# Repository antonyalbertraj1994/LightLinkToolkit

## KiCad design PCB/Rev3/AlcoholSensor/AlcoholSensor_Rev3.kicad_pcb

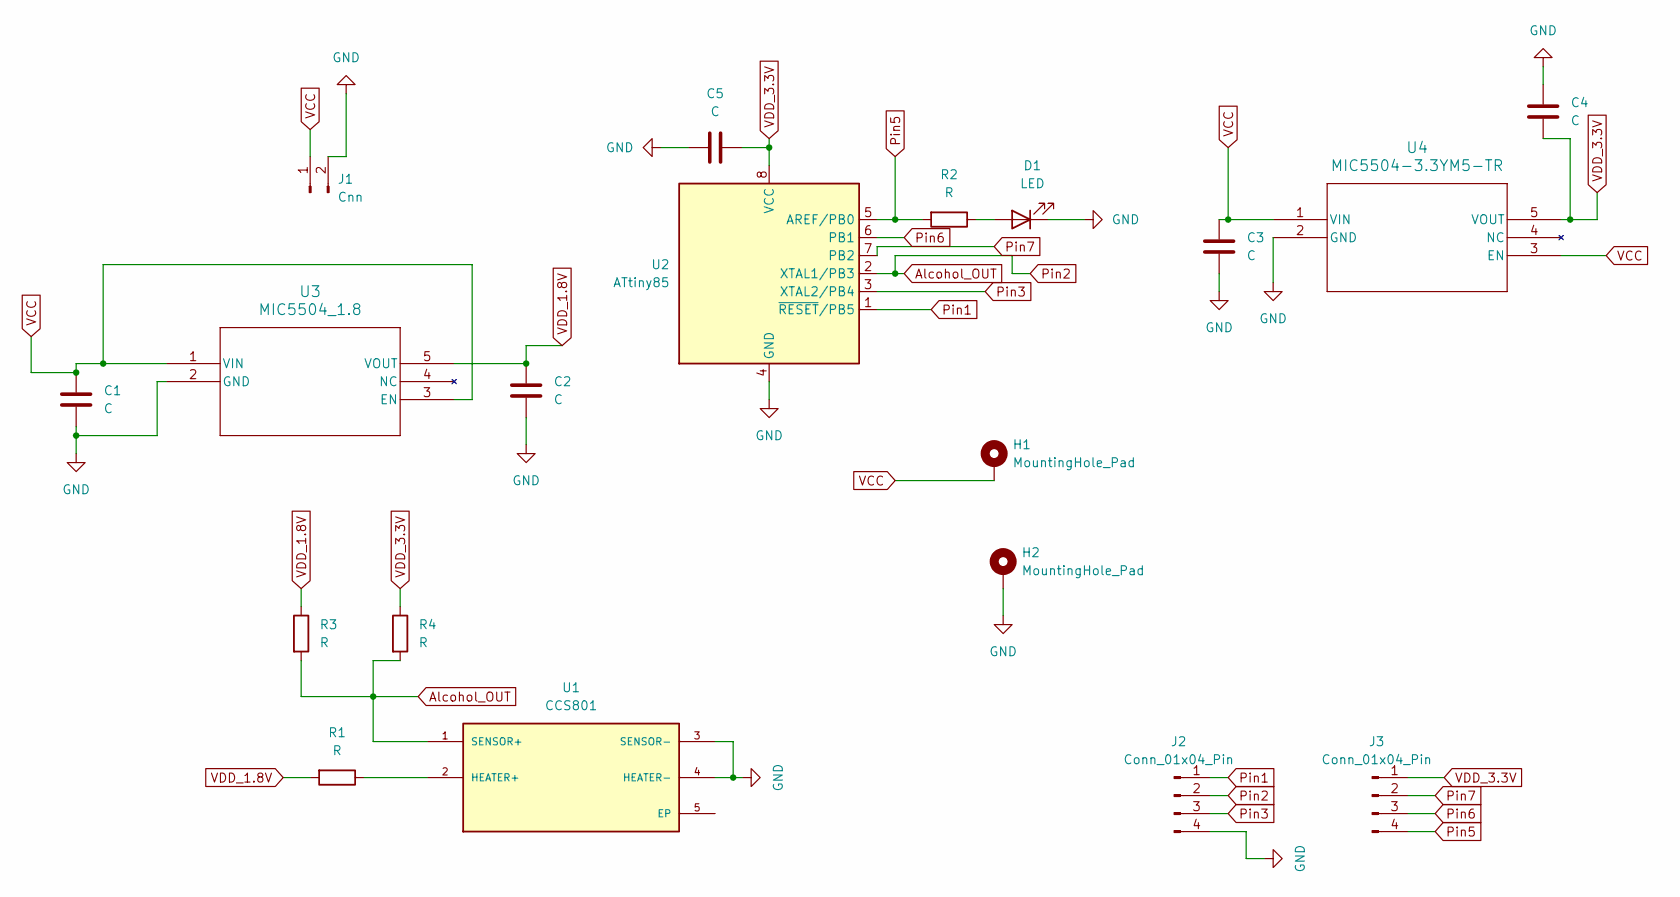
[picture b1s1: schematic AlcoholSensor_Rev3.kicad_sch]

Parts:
C1, C2, C3, C4, C5: C; C_0603_1608Metric_Pad1.08x0.95mm_HandSolder
D1: LED; LED_0805_2012Metric_Pad1.15x1.40mm_HandSolder
H1, H2: MountingHole_Pad; MT_Hole
J1: Cnn; PinHeader_1x02_P2.54mm_Vertical
J2, J3: Conn_01x04_Pin; PinHeader_1x04_P1.27mm_Vertical
R1, R2, R3, R4: R; R_0603_1608Metric_Pad0.98x0.95mm_HandSolder
U1: CCS801; XDCR_CCS801; PARTREV v1-04
U2: ATtiny85; SOIC-8W_5.3x5.3mm_P1.27mm
U3: MIC5504_1.8; SOT23-5LD-PL-1_MCH
U4: MIC5504-3.3YM5-TR; SOT-23-5_MC_MCH

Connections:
Alcohol_OUT: J2.2, R3.2, R4.2, U1.1 (SENSOR+), U2.2 (XTAL1/PB3)
GND: C1.2, C2.2, C3.2, C4.2, C5.1, D1.1 (K), H2.1, J1.2, J2.4, U1.3 (SENSOR-), U1.4 (HEATER-), U2.4 (GND), U3.2 (GND), U4.2 (GND)
unnamed: D1.2 (A), R2.1
unnamed: R1.1, U1.2 (HEATER+)
Pin1: J2.1, U2.1 (~RESET/PB5)
Pin3: J2.3, U2.3 (XTAL2/PB4)
Pin5: J3.4, R2.2, U2.5 (AREF/PB0)
Pin6: J3.3, U2.6 (PB1)
Pin7: J3.2, U2.7 (PB2)
VCC: C1.1, C3.1, H1.1, J1.1, U3.1 (VIN), U3.3 (EN), U4.1 (VIN), U4.3 (EN)
VDD_1.8V: C2.1, R1.2, R3.1, U3.5 (VOUT)
VDD_3.3V: C4.1, C5.2, J3.1, R4.1, U2.8 (VCC), U4.5 (VOUT)

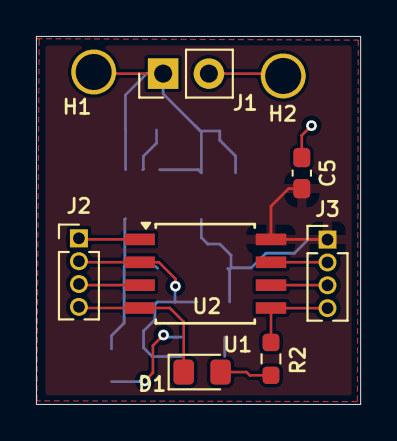
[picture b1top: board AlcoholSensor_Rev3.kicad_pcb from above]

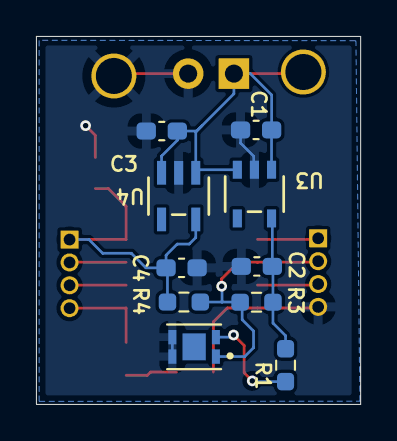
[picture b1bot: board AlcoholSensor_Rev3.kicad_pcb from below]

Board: 2 copper layers, 18.0 x 20.4 mm, 19 parts (10 on the bottom side), 12 nets.

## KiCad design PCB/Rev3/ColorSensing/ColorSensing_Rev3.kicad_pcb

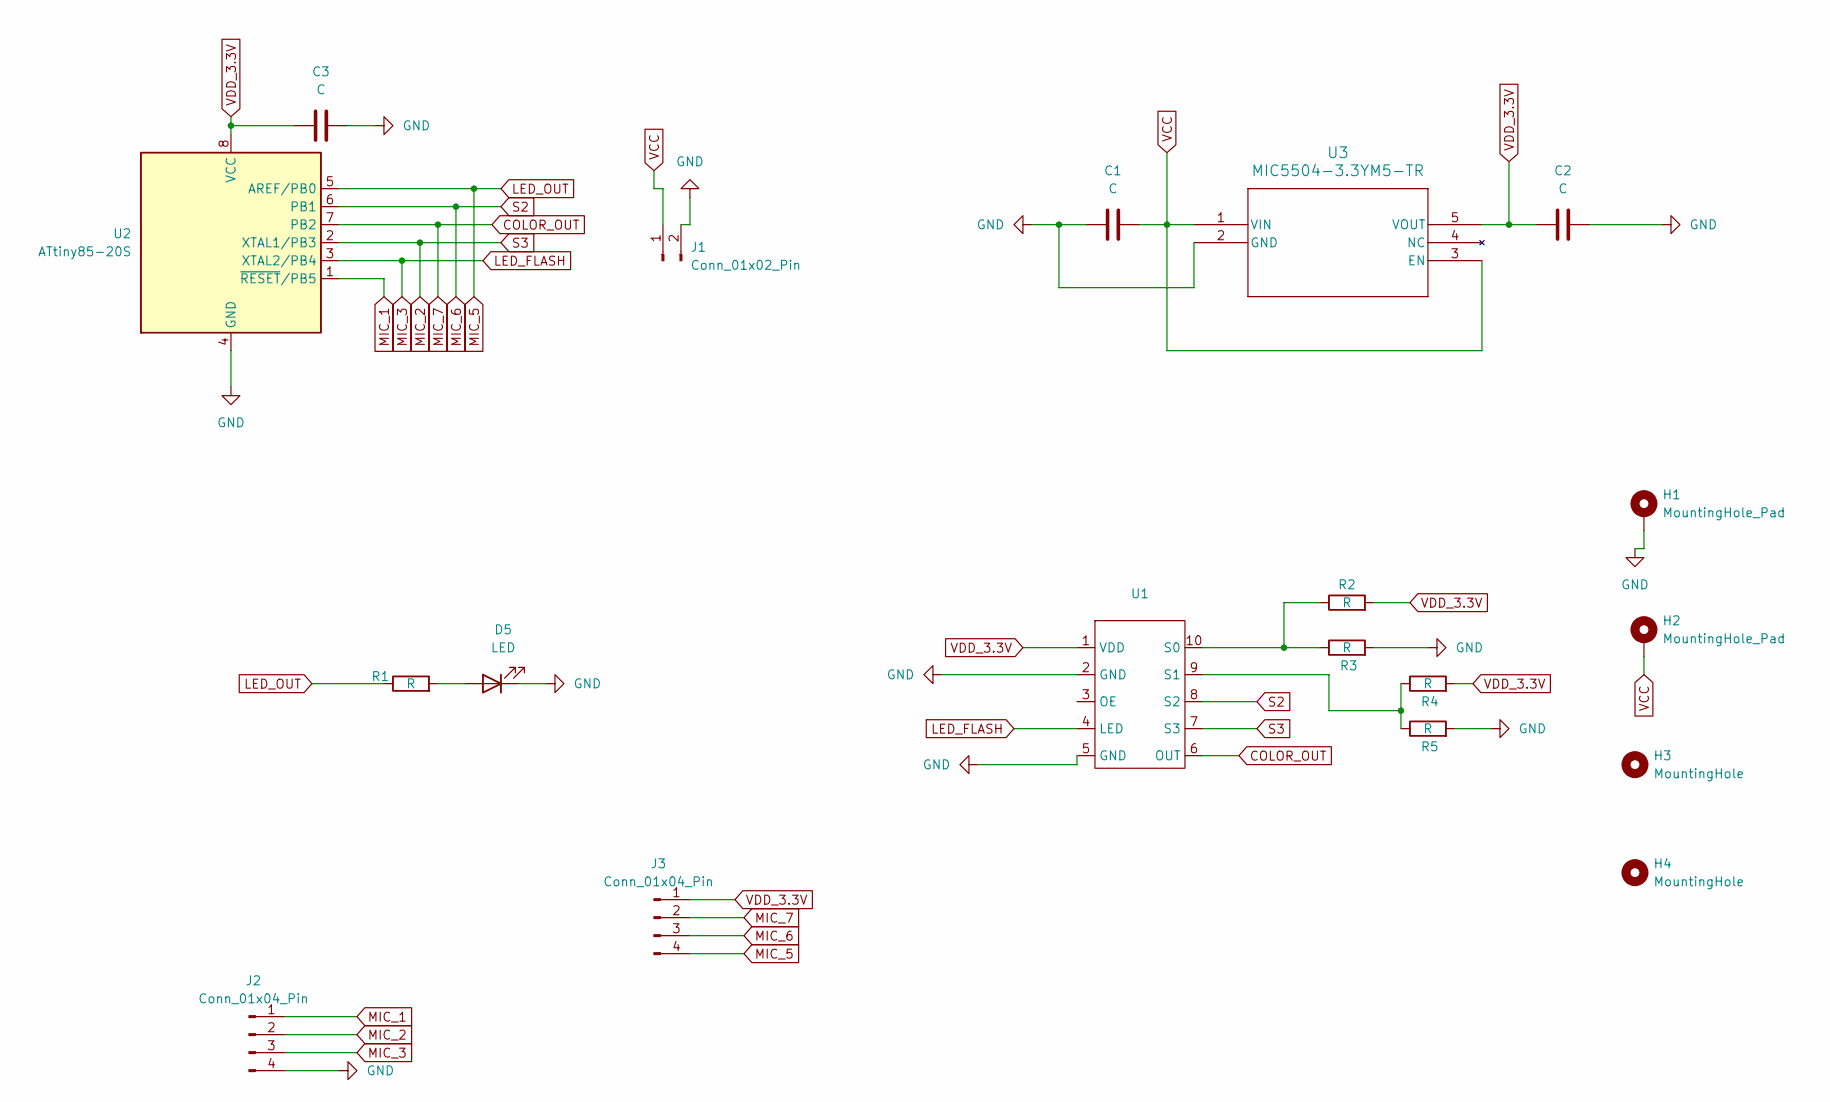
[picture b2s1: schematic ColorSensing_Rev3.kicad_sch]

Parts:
C1, C2, C3: C; C_0603_1608Metric_Pad1.08x0.95mm_HandSolder
D5: LED; LED_0805_2012Metric_Pad1.15x1.40mm_HandSolder
H1, H2: MountingHole_Pad; MT_Hole
H3, H4: MountingHole; MT_Hole
J1: Conn_01x02_Pin; PinHeader_1x02_P2.54mm_Vertical
J2, J3: Conn_01x04_Pin; PinHeader_1x04_P2.54mm_Vertical
R1, R2, R3, R4, R5: R; R_0603_1608Metric_Pad0.98x0.95mm_HandSolder
U1: TCS3200_DFR
U2: ATtiny85-20S; SOIC-8W_5.3x5.3mm_P1.27mm
U3: MIC5504-3.3YM5-TR; SOT-23-5_MC_MCH

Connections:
COLOR_OUT: J3.2, U1.6 (OUT), U2.7 (PB2)
GND: C1.1, C2.2, C3.2, D5.1 (K), H1.1, J1.2, J2.4, R3.2, R5.2, U1.2 (GND), U1.5 (GND), U2.4 (GND), U3.2 (GND)
LED_FLASH: J2.3, U1.4 (LED), U2.3 (XTAL2/PB4)
LED_OUT: J3.4, R1.1, U2.5 (AREF/PB0)
MIC_1: J2.1, U2.1 (~RESET/PB5)
MIC_2: J2.2, U1.7 (S3), U2.2 (XTAL1/PB3)
MIC_6: J3.3, U1.8 (S2), U2.6 (PB1)
unnamed: D5.2 (A), R1.2
unnamed: R2.1, R3.1, U1.10 (S0)
unnamed: R4.1, R5.1, U1.9 (S1)
VCC: C1.2, H2.1, J1.1, U3.1 (VIN), U3.3 (EN)
VDD_3.3V: C2.1, C3.1, J3.1, R2.2, R4.2, U1.1 (VDD), U2.8 (VCC), U3.5 (VOUT)

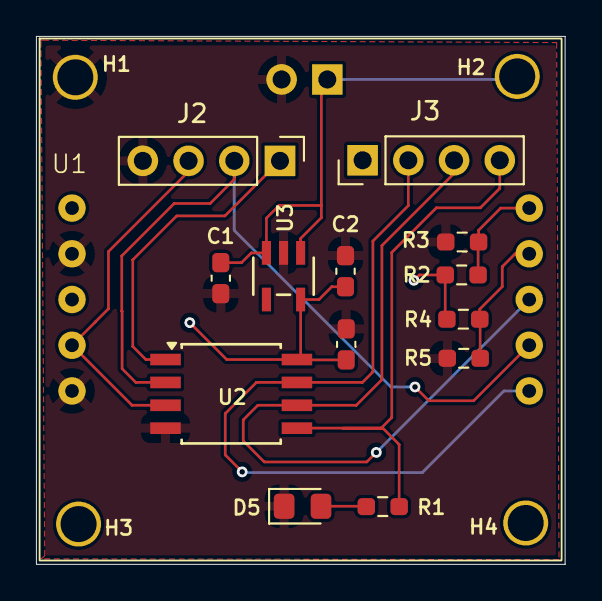
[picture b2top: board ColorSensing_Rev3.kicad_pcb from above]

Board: 2 copper layers, 29.4 x 29.3 mm, 19 parts (1 on the bottom side), 12 nets.
